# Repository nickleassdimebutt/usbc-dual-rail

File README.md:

# usbc-dual-rail

USB-C-powered dual-rail breakout — both 5 V (passthrough from USB) AND
3.3 V (via AMS1117 LDO) on separate 2-pin headers, each with a colour-
coded power-good LED (yellow for 5 V, green for 3.3 V).

PCBA-3 test project for the [kicad-claude-toolkit](https://github.com/nickleassdimebutt/kicad-claude-toolkit)
v3 toolchain. Same component count as usbc-3v3 (15) but a different
topology — exercises the toolkit on a multi-rail design.

## Layout status

The validated routes from usbc-3v3 (J1 escape, VBUS bus stub, CC
pulldowns, GND bridges) are reused verbatim. The 5 V branch (D2/R10
power-LED + J2 5V_OUT header) and the +3V3 branch updates (J3 3V3_OUT)
are deferred to KiCad GUI hand-routing.

DRC: 2 minor violations (1 dangling track endpoint, 1 silk edge
clearance — both fixable by trimming) and 9 unconnected items (the
routing TODO).

## Build

```powershell
& "C:\Program Files\KiCad\10.0\bin\python.exe" build.py --datasheet --sim
```

## Topology summary

| Block | Components | Function |
|-------|------------|----------|
| `usbc_power` | J1 + R1, R2 | USB-C 5 V input + CC pulldowns |
| `ldo` | U1 + C1, C2, C3 | AMS1117-3.3 LDO with bypass caps |
| `led` (5 V) | D2 + R10 | Yellow 5 V power-good indicator |
| `led` (3 V) | D1 + R3 | Green 3.3 V power-good indicator |
| `header` | J2, J3 | Two 2-pin output headers (5V_OUT, 3V3_OUT) |
| `mounting` | H1, H2 | Two M2 corner holes |

15 components, 7 nets, 50 × 30 mm.

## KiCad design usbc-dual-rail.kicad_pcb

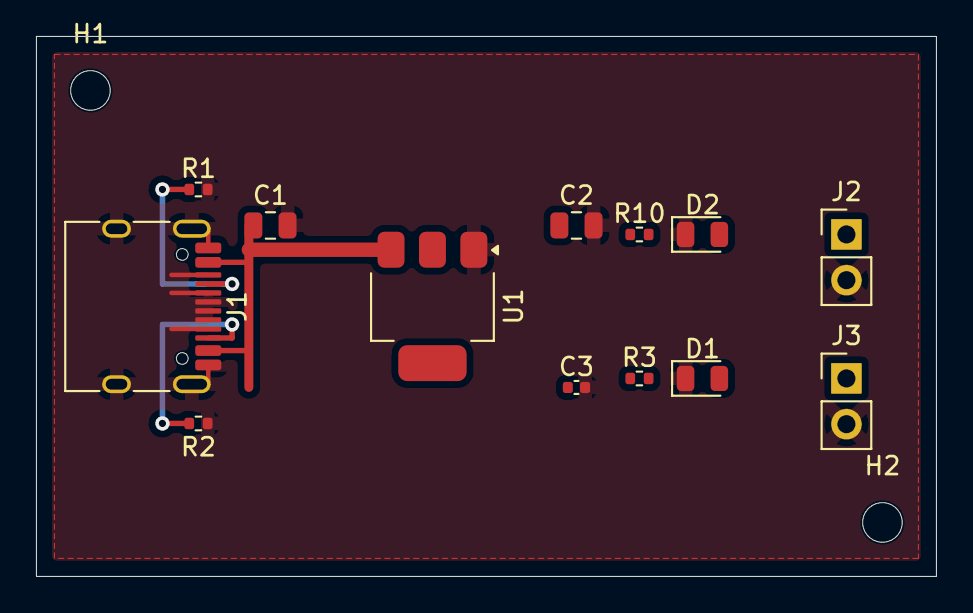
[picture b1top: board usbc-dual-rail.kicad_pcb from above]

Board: 2 copper layers, 50.0 x 30.0 mm, 15 parts (0 on the bottom side), 7 nets.

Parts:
C1, C2: 10uF; C_0805_2012Metric
C3: 100nF; C_0402_1005Metric
D1: GREEN; LED_0805_2012Metric
D2: YELLOW; LED_0805_2012Metric
H1, H2: MountingHole_M2; MountingHole_2.2mm_M2
J1: HRO TYPE-C-31-M-12; USB_C_Receptacle_HRO_TYPE-C-31-M-12
J2: 5V_OUT; PinHeader_1x02_P2.54mm_Vertical
J3: 3V3_OUT; PinHeader_1x02_P2.54mm_Vertical
R1, R2: 5.1k; R_0402_1005Metric
R3: 820.0; R_0402_1005Metric
R10: 1.8k; R_0402_1005Metric
U1: AMS1117-3.3; SOT-223-3_TabPin2

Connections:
+3V3: C2.1, C3.1, J3.1, R3.1, U1.2
CC1: J1.A5, R1.1
CC2: J1.B5, R2.1
GND: C1.2, C2.2, C3.2, D1.1, D2.1, J1.A1, J1.A6, J1.A7, J1.A8, J1.A12, J1.B1, J1.B6, J1.B7, J1.B8, J1.B12, J1.SH, J2.2, J3.2, R1.2, R2.2, U1.1
N_D1: D1.2, R3.2
N_D2: D2.2, R10.2
VBUS: C1.1, J1.A4, J1.A9, J1.B4, J1.B9, J2.1, R10.1, U1.3
